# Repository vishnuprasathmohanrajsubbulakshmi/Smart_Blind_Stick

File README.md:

# VL53L8CX Sensor Project

This project demonstrates how to use the VL53L8CX distance sensor with an Arduino platform. The code initializes three VL53L8CX sensors, reads their distance measurements, and controls motor speed based on the detected distance.

## Features

- Initializes three VL53L8CX sensors via I2C.
- Reads distance data and prints results to the Serial Monitor.
- Controls motor speed based on detected distance:
  - Near (0-10 mm): High speed
  - Medium (10-250 mm): Medium speed
  - Far (250-1000 mm): Low speed
  - No object detected: Stop

## Components Required

- Arduino board (compatible with the SAM DUE)
- VL53L8CX distance sensors (3 units)
- Motors (3 units)
- Motor driver or similar circuit for controlling motor speed
- Jumper wires
- Breadboard (optional)

## Wiring Diagram

1. **VL53L8CX Sensors:**
   - Connect each sensor to the I2C pins of the Arduino.
   - Use defined power and ground pins for enabling sensors.

2. **Motors:**
   - Connect motors to the specified power pins (`PWR_MOT_1`, `PWR_MOT_2`, `PWR_MOT_3`).
   - Ensure ground is connected.

## Installation

1. Clone the repository:

   ```bash
   git clone https://github.com/yourusername/vl53l8cx-sensor-project.git

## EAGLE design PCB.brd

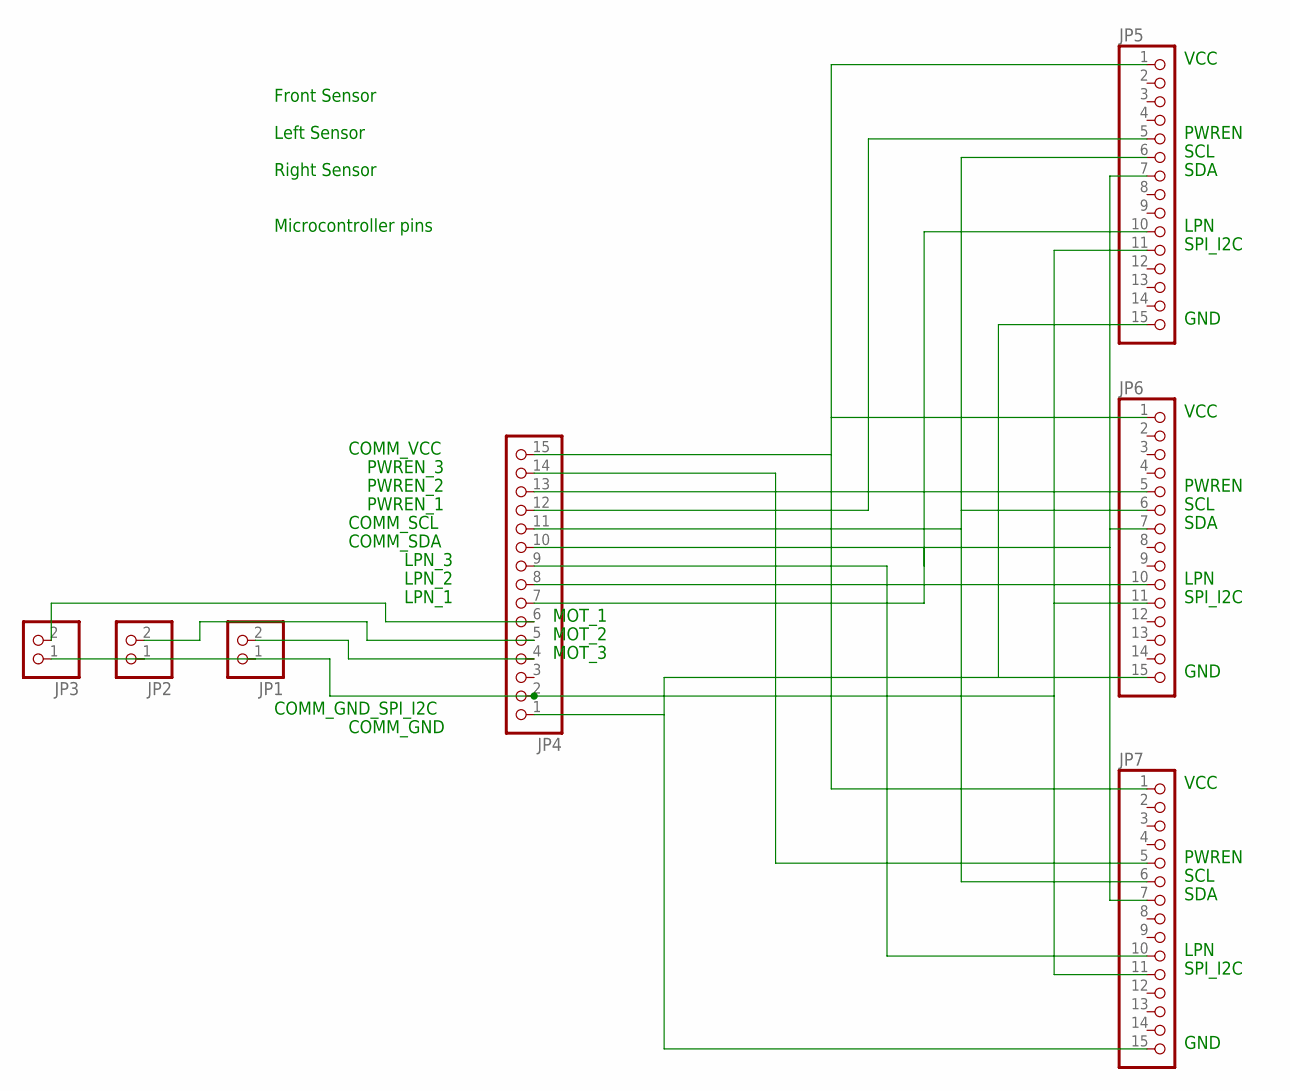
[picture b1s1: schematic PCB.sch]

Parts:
JP1, JP2, JP3: PINHD-1X2; 1X02
JP4, JP5, JP6, JP7: PINHD-1X15; 1X15

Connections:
unnamed: JP4.15, JP5.1, JP6.1, JP7.1
unnamed: JP4.1, JP5.15, JP6.15, JP7.15
unnamed: JP4.7, JP4.10, JP5.7, JP6.7, JP7.7
unnamed: JP4.11, JP5.6, JP6.6, JP7.6
unnamed: JP4.12, JP5.5
unnamed: JP4.13, JP6.5
unnamed: JP4.14, JP7.5
unnamed: JP4.8, JP6.10
unnamed: JP4.9, JP7.10
unnamed: JP1.1, JP4.2, JP5.11, JP6.11, JP7.11
unnamed: JP2.1, JP3.1
unnamed: JP3.2, JP4.6
unnamed: JP2.2, JP4.5
unnamed: JP1.2, JP4.4

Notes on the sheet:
COMM_VCC
COMM_GND
VCC
PWREN
SCL
SDA
LPN
SPI_I2C
GND
PWREN_1
PWREN_2
PWREN_3
COMM_SCL
COMM_SDA
LPN_3
LPN_2
LPN_1
COMM_GND_SPI_I2C
MOT_1
MOT_2
MOT_3
Front Sensor
Left Sensor
Right Sensor
Microcontroller pins

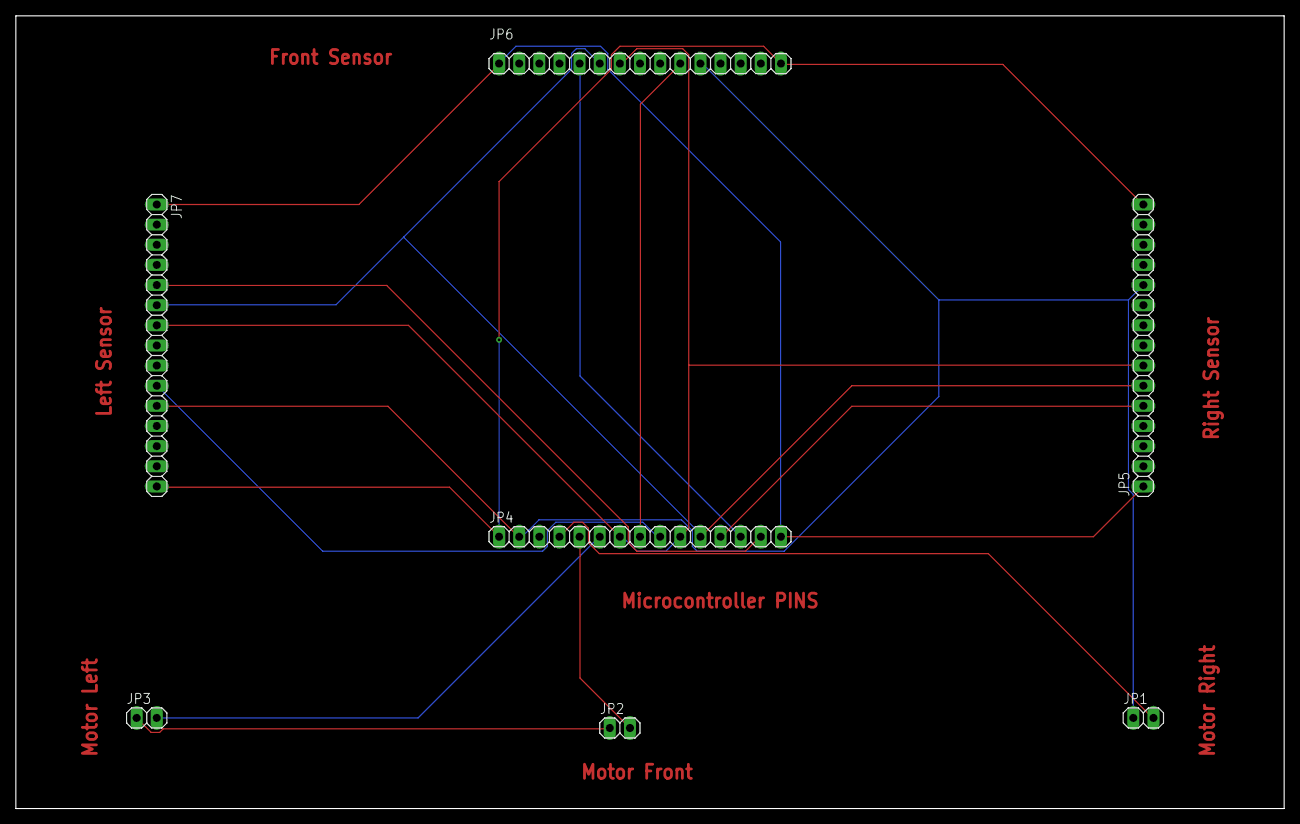
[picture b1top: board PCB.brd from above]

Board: 2 copper layers, 160.0 x 100.0 mm, 7 parts (0 on the bottom side), 14 nets.

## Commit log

2024-10-05 .ino code for VL53L8CX TOF Sensor for Blind Stick
2024-10-05 PCB SCH and BRD File for Blind Stick Sensor
